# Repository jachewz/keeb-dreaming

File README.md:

# keeb-dreaming
Build a 68% keyboard pcb and case

Assembled keyboard (bought the caps and switches):

## Features
- USB-C
- Volume knob + mute button
- Compression fit of pcb with case, no fasteners needed

## PCB

- Learned from https://wiki.ai03.com/books/pcb-design/chapter/pcb-designer-guide
- Use KiCAD to edit the schematics and pcb design

## Firmware
- Copy [this folder](qmk/zap) into the [QMK repository's keyboards folder](https://github.com/qmk/qmk_firmware/tree/master/keyboards)
- Use the [QMK MSYS terminal tool](https://docs.qmk.fm/#/newbs_getting_started) and run `qmk compile -kb zap -km default`
- Alternatively, if you have a c compiler and make installed, run `make zap`
#### Flashing
- `make zap:default:flash`
- If that does not work try power cycling/resetting while shorting the BOOT0 pin to ground (exposed on the PCB, feel free to solder a switch on it).
- Use the [STM32 programmer](https://www.st.com/en/development-tools/stm32cubeprog.html) for further debugging and validating.

## Case

- In the picture above is this [case](case/3d), 3D printed, modeled using SolidWorks (free-trial)
- A layered version is also in the [case/layered](case/layered) folder

### Note
- The tolerance of the case is very small with the PCB, super tight fitting. Probably because 3D prints expand. Adjust the sizing of either the case or the PCB, and use M2 screws to fasten if needed.
- The USB-C hole needs to be higher/taller, make sure to edit it to leave at most 10mm material from the edge. The one in the picture had its hole expanded post production.
- Adding to the point above, foam can be added below but may change the placing of the USB-C hole.

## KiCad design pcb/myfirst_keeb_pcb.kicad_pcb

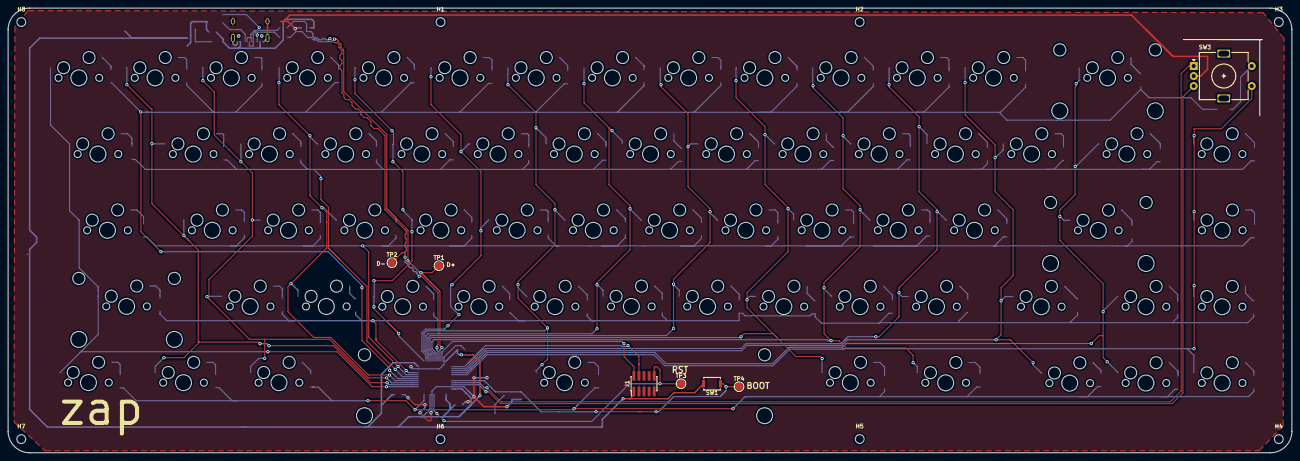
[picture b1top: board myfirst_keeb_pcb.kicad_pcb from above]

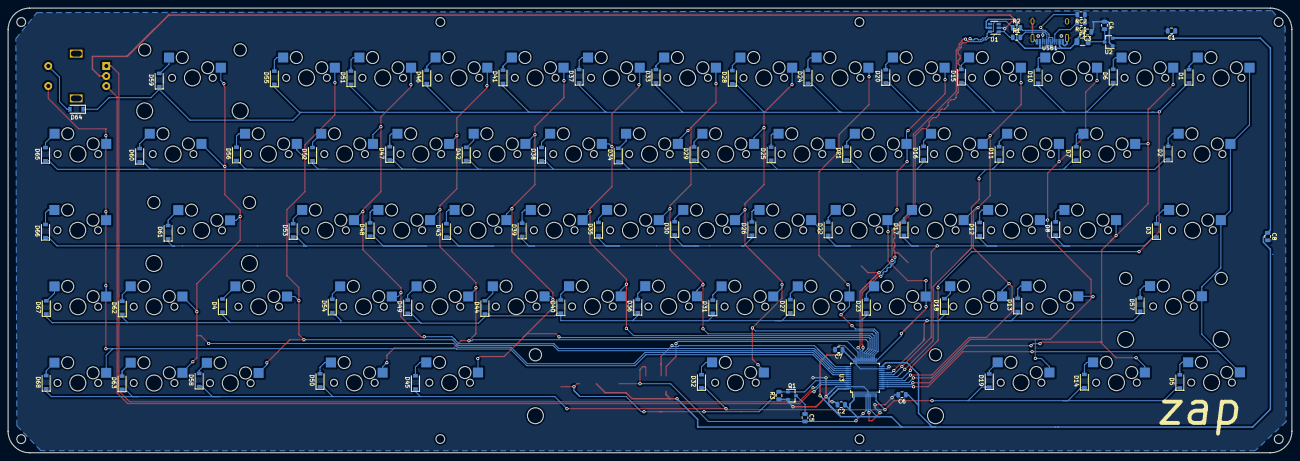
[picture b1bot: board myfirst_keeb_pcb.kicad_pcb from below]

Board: 2 copper layers, 320.9 x 111.1 mm, 167 parts (86 on the bottom side), 104 nets.

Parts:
C1, C2, C3, C4, C6, C7: 100nF; C_0805_2012Metric
C5: 100uF; C_0805_2012Metric
C8: 4.7uF; C_0805_2012Metric
D1, D2, D3, D4, D5, D6, D7, D8, D10, D11, D12, D13, D14, D15, D16, D17, D18, D19, D20, D21, D22, D23, D24, D25, D26, D27, D28, D29, D30, D31, D32, D33, D34, D35, D36, D37, D38, D39, D40, D41, D42, D43, D44, D45, D46, D47, D48, D49, D50, D51, D52, D53, D54, D55, D56, D57, D58, D59, D60, D61, D62, D63, D64, D65, D66, D67, D68: SOD_123; D_SOD-123
F1: 500mA; Fuse_1206_3216Metric
H1, H2, H3, H4, H5, H6, H7, H8: MountingHole; MountingHole_2.2mm_M2
J1: Conn_ARM_JTAG_SWD_10; PinHeader_2x05_P1.27mm_Vertical_SMD
MX1: ESC; MXOnly-1U-Hotswap
MX2: Tab; MXOnly-1.5U-Hotswap
MX3: CapsLk; MXOnly-1.75U-Hotswap
MX4: RShift; MXOnly-1.75U-Hotswap
MX5: Ctrl; MXOnly-1.25U-Hotswap
MX6: 1; MXOnly-1U-Hotswap
MX7: Q; MXOnly-1U-Hotswap
MX8: A; MXOnly-1U-Hotswap
MX10: 2; MXOnly-1U-Hotswap
MX11: W; MXOnly-1U-Hotswap
MX12: S; MXOnly-1U-Hotswap
MX13: Z; MXOnly-1U-Hotswap
MX14: Super; MXOnly-1.25U-Hotswap
MX15: 3; MXOnly-1U-Hotswap
MX16: E; MXOnly-1U-Hotswap
MX17: D; MXOnly-1U-Hotswap
MX18: X; MXOnly-1U-Hotswap
MX19: LAlt; MXOnly-1.25U-Hotswap
MX20: 4; MXOnly-1U-Hotswap
MX21: R; MXOnly-1U-Hotswap
MX22: F; MXOnly-1U-Hotswap
MX23: C; MXOnly-1U-Hotswap
MX24: 5; MXOnly-1U-Hotswap
MX25: T; MXOnly-1U-Hotswap
MX26: G; MXOnly-1U-Hotswap
MX27: V; MXOnly-1U-Hotswap
MX28: 6; MXOnly-1U-Hotswap
MX29: Y; MXOnly-1U-Hotswap
MX30: H; MXOnly-1U-Hotswap
MX31: B; MXOnly-1U-Hotswap
MX32: Space; MXOnly-6.25U-Hotswap
MX33: 7; MXOnly-1U-Hotswap
MX34: U; MXOnly-1U-Hotswap
MX35: J; MXOnly-1U-Hotswap
MX36: N; MXOnly-1U-Hotswap
MX37: 8; MXOnly-1U-Hotswap
MX38: I; MXOnly-1U-Hotswap
MX39: K; MXOnly-1U-Hotswap
MX40: M; MXOnly-1U-Hotswap
MX41: 9; MXOnly-1U-Hotswap
MX42: O; MXOnly-1U-Hotswap
MX43: L; MXOnly-1U-Hotswap
MX44: ,; MXOnly-1U-Hotswap
MX45: RAlt; MXOnly-1.25U-Hotswap
MX46: 0; MXOnly-1U-Hotswap
MX47: P; MXOnly-1U-Hotswap
MX48: ;; MXOnly-1U-Hotswap
MX49: .; MXOnly-1U-Hotswap
MX50: Fn; MXOnly-1.25U-Hotswap
MX51: _; MXOnly-1U-Hotswap
MX52: {; MXOnly-1U-Hotswap
MX53: "; MXOnly-1U-Hotswap
MX54: /; MXOnly-1U-Hotswap
MX55: +; MXOnly-1U-Hotswap
MX56: }; MXOnly-1U-Hotswap
MX57: LShift; MXOnly-2.25U-Hotswap
MX58: Left; MXOnly-1U-Hotswap
MX59: Backspace; MXOnly-2U-Hotswap
MX60: |; MXOnly-1.5U-Hotswap
MX61: Enter; MXOnly-2.25U-Hotswap
MX62: Up; MXOnly-1U-Hotswap
MX63: Down; MXOnly-1U-Hotswap
MX64: Del; MXOnly-1U-Hotswap
MX65: PageUp; MXOnly-1U-Hotswap
MX66: PageDown; MXOnly-1U-Hotswap
MX67: Right; MXOnly-1U-Hotswap
Q1: DTC123J; SOT-23
R1, R2: 22; R_0805_2012Metric
R3: 10k; R_0805_2012Metric
RC1, RC2: 5k1; R_0805_2012Metric
SW1: SW_Push; SW_Push_SPST_NO_Alps_SKRK
SW3: Rotary_Encoder_Switch; RotaryEncoder_Alps_EC11E-Switch_Vertical_H20mm
TP1, TP2, TP3, TP4: TestPoint; TestPoint_Pad_D2.0mm
U1: SRV05-4; SOT-23-6
U2: MCP1700-3302E_SOT23; SOT-23
U3: STM32F072CBTx; LQFP-48_7x7mm_P0.5mm
USB1: HRO-TYPE-C-31-M-12; HRO-TYPE-C-31-M-12-Assembly

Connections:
+3V3: C1.1, C2.1, C6.1, C7.1, C8.1, J1.1, SW1.2, U2.2, U3.1, U3.9, U3.24, U3.36, U3.48
BOOT0: Q1.1, R3.2, SW1.1, TP4.1, U3.44
COL0: MX1.1, MX2.1, MX3.1, MX5.1, MX57.1, U3.14
COL1: MX6.1, MX7.1, MX8.1, MX14.1, U3.15
COL2: MX10.1, MX11.1, MX12.1, MX13.1, MX19.1, U3.16
COL3: MX15.1, MX16.1, MX17.1, MX18.1, U3.17
COL4: MX20.1, MX21.1, MX22.1, MX23.1, U3.25
COL5: MX24.1, MX25.1, MX26.1, MX27.1, U3.26
COL6: MX28.1, MX29.1, MX30.1, MX31.1, MX32.1, U3.27
COL7: MX33.1, MX34.1, MX35.1, MX36.1, U3.28
COL8: MX37.1, MX38.1, MX39.1, MX40.1, U3.29
COL9: MX41.1, MX42.1, MX43.1, MX44.1, MX45.1, U3.30
COL10: MX46.1, MX47.1, MX48.1, MX49.1, MX50.1, U3.31
COL11: MX51.1, MX52.1, MX53.1, MX54.1, U3.38
COL12: MX4.1, MX55.1, MX56.1, MX58.1, U3.39
COL13: MX59.1, MX60.1, MX61.1, MX62.1, MX63.1, U3.40
COL14: MX64.1, MX65.1, MX66.1, MX67.1, SW3.S1, U3.41
D+: R1.1, TP1.1, U1.1, U3.33
D-: R2.1, TP2.1, U1.6, U3.32
ENCODER_A: SW3.A, U3.45
ENCODER_B: SW3.B, U3.46
GND: C1.2, C2.2, C3.1, C4.1, C6.2, C7.2, C8.2, J1.3, J1.5, J1.9, Q1.2, R3.1, RC1.1, RC2.1, SW3.C, U1.2, U2.1, U3.8, U3.23, U3.35, U3.47, USB1.1, USB1.12, USB1.13
NRST: C5.2, J1.10, TP3.1, U3.7
unnamed: C4.2, F1.2, U2.3
unnamed: C5.1, Q1.3
unnamed: D1.2, MX1.2
unnamed: D2.2, MX2.2
unnamed: D3.2, MX3.2
unnamed: D4.2, MX4.2
unnamed: D5.2, MX5.2
unnamed: D6.2, MX6.2
unnamed: D7.2, MX7.2
unnamed: D8.2, MX8.2
unnamed: D10.2, MX10.2
unnamed: D11.2, MX11.2
unnamed: D12.2, MX12.2
unnamed: D13.2, MX13.2
unnamed: D14.2, MX14.2
unnamed: D15.2, MX15.2
unnamed: D16.2, MX16.2
unnamed: D17.2, MX17.2
unnamed: D18.2, MX18.2
unnamed: D19.2, MX19.2
unnamed: D20.2, MX20.2
unnamed: D21.2, MX21.2
unnamed: D22.2, MX22.2
unnamed: D23.2, MX23.2
unnamed: D24.2, MX24.2
unnamed: D25.2, MX25.2
unnamed: D26.2, MX26.2
unnamed: D27.2, MX27.2
unnamed: D28.2, MX28.2
unnamed: D29.2, MX29.2
unnamed: D30.2, MX30.2
unnamed: D31.2, MX31.2
unnamed: D32.2, MX32.2
unnamed: D33.2, MX33.2
unnamed: D34.2, MX34.2
unnamed: D35.2, MX35.2
unnamed: D36.2, MX36.2
unnamed: D37.2, MX37.2
unnamed: D38.2, MX38.2
unnamed: D39.2, MX39.2
unnamed: D40.2, MX40.2
unnamed: D41.2, MX41.2
unnamed: D42.2, MX42.2
unnamed: D43.2, MX43.2
unnamed: D44.2, MX44.2
unnamed: D45.2, MX45.2
unnamed: D46.2, MX46.2
unnamed: D47.2, MX47.2
unnamed: D48.2, MX48.2
unnamed: D49.2, MX49.2
unnamed: D50.2, MX50.2
unnamed: D51.2, MX51.2
unnamed: D52.2, MX52.2
unnamed: D53.2, MX53.2
unnamed: D54.2, MX54.2
unnamed: D55.2, MX55.2
unnamed: D56.2, MX56.2
unnamed: D57.2, MX57.2
unnamed: D58.2, MX58.2
unnamed: D59.2, MX59.2
unnamed: D60.2, MX60.2
unnamed: D61.2, MX61.2
unnamed: D62.2, MX62.2
unnamed: D63.2, MX63.2
unnamed: D64.2, SW3.S2
unnamed: D65.2, MX64.2
unnamed: D66.2, MX65.2
unnamed: D67.2, MX66.2
unnamed: D68.2, MX67.2
unnamed: R1.2, USB1.6, USB1.8
unnamed: R2.2, USB1.5, USB1.7
unnamed: RC1.2, USB1.4
unnamed: RC2.2, USB1.10
ROW0: D1.1, D6.1, D10.1, D15.1, D20.1, D24.1, D28.1, D33.1, D37.1, D41.1, D46.1, D51.1, D55.1, D59.1, D64.1, U3.18
ROW1: D2.1, D7.1, D11.1, D16.1, D21.1, D25.1, D29.1, D34.1, D38.1, D42.1, D47.1, D52.1, D56.1, D60.1, D65.1, U3.19
ROW2: D3.1, D8.1, D12.1, D17.1, D22.1, D26.1, D30.1, D35.1, D39.1, D43.1, D48.1, D53.1, D61.1, D66.1, U3.20
ROW3: D4.1, D13.1, D18.1, D23.1, D27.1, D31.1, D36.1, D40.1, D44.1, D49.1, D54.1, D57.1, D62.1, D67.1, U3.21
ROW4: D5.1, D14.1, D19.1, D32.1, D45.1, D50.1, D58.1, D63.1, D68.1, U3.12
SWDCLK: J1.4, U3.37
SWDIO: J1.2, U3.34
VCC: C3.2, F1.1, U1.5, USB1.2, USB1.11

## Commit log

2021-10-10 Initialize
2021-10-10 adding drawings and rearranging folders
2021-10-11 symbol % footprint tables
2021-10-11 update files to 5.0+
2021-10-12 Schematics - ATmega, USB
2021-10-16 add sample of mx schematic
2021-10-26 Add matrix and change to STM32f303
2021-11-02 Assign 1u+ key footprints Half arranged layout
2021-11-07 key layout complete. Diode todo
2021-11-08 diode layout complete added case graphics on pcb
2022-04-17 pcb wip
2022-09-25 change stm32 chip to STM32F410CBT6
2023-02-18 complete routing
2023-02-20 fix track errors
    - hole too close error irrelevant because that is from the mx switch library and its meant to be
    - usb pads should be close together, its from the part's library
2023-02-21 add cringe deco text
2023-02-23 remove switch for rst, use same switch as BOOT0 - add jtag for swd
2023-03-11 moved boot button to directly under spacebar
    - easy push
2023-03-13 shorten and made data bus lengths similar
    - fix row trace unconnected
2023-04-18 add M2 mounting holes & rounded board cut-out
2023-04-22 change microcontroller cause no stock
    - shifted microcontroller position little bit nearer to usb
    - fixed filling zones
2023-04-22 move rc1 and rc2 to bottom side. adjust data line length to be similar. adjust filling zone dimensions
2023-04-22 change boot button switch footprint - smaller and more available
2023-04-22 flip boot switch and jtag conn to top
2023-09-19 add qmk fw config
2023-10-09 switch stm32f11 to stm32f07 for usb crystal
2023-10-10 change to hotswap kalih switches
2024-06-25 update kicad version
2024-06-25 upload photos of product
2024-06-25 add case design files
